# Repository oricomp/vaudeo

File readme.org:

#+title: vaudeo

A Video and Audio Board for the OriComp System

#+CAPTION: Vaudeo Logo
#+ATTR_ORG: :align center
#+ATTR_HTML: :align center
[[https://github.com/oricomp/vaudeo/blob/main/docs/logo/vaudeo_logo_gray.png]]

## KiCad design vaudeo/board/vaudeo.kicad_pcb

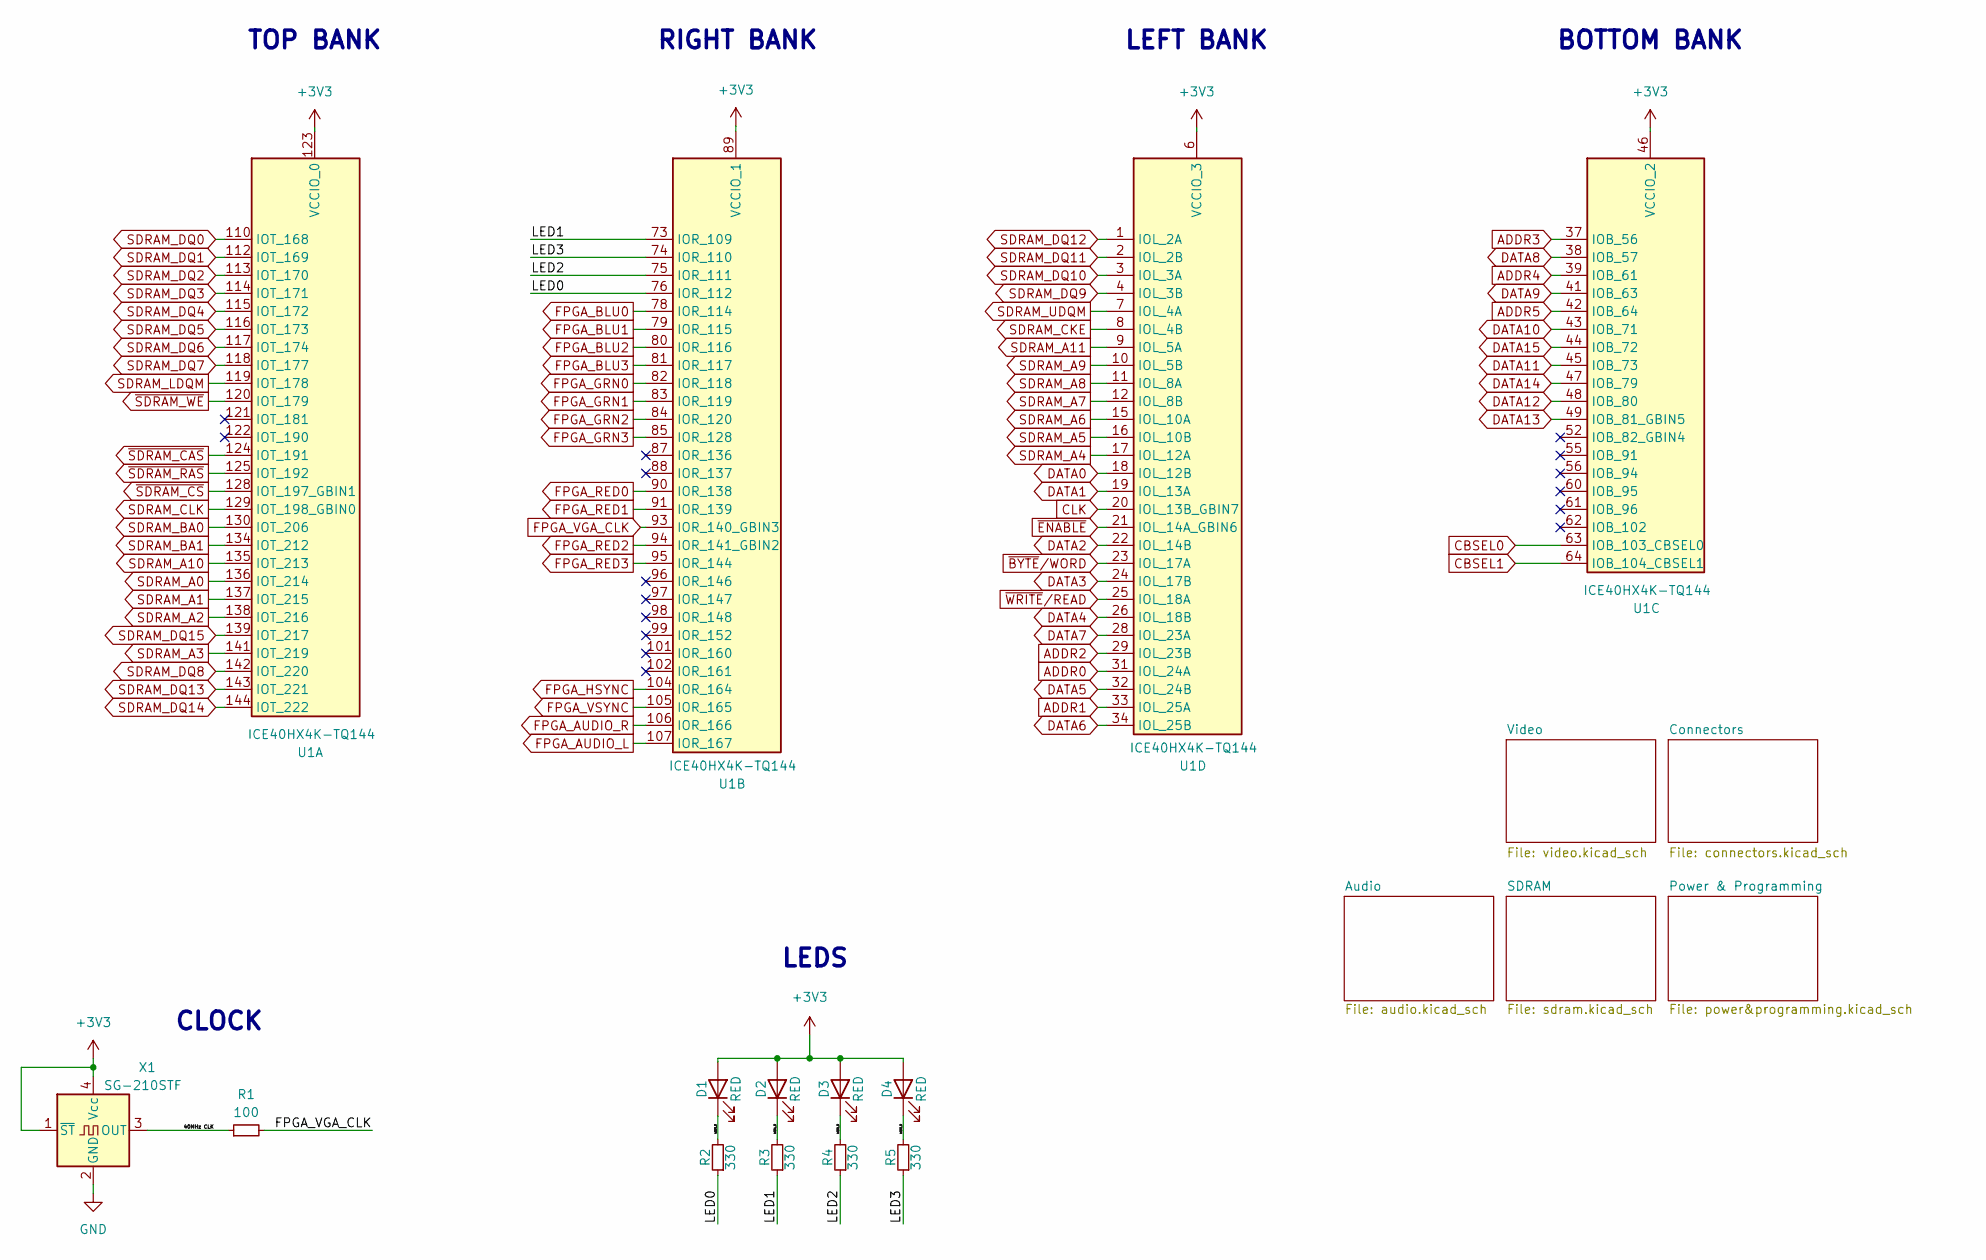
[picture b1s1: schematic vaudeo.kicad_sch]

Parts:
D1, D2, D3, D4: RED; D_0805_2012Metric
R1: 100; R_0805_2012Metric_Pad1.20x1.40mm_HandSolder
R2, R3, R4, R5: 330; R_0805_2012Metric_Pad1.20x1.40mm_HandSolder
U1: ICE40HX4K-TQ144; TQFP-144_20x20mm_P0.5mm
X1: SG-210STF; Oscillator_SMD_SeikoEpson_SG210-4Pin_2.5x2.0mm

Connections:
+3V3: D1.2 (A), D2.2 (A), D3.2 (A), D4.2 (A), U1.6 (VCCIO_3), U1.30 (VCCIO_3), U1.46 (VCCIO_2), U1.57 (VCCIO_2), U1.89 (VCCIO_1), U1.100 (VCCIO_1), U1.123 (VCCIO_0), U1.131 (VCCIO_0), X1.1 (~ST), X1.4 (Vcc); also elsewhere on the board
/40MHz CLK: R1.1, X1.3 (OUT)
/LED0: R2.1, U1.76 (IOR_112)
/LED0_R: D1.1 (K), R2.2
/LED1: R3.1, U1.73 (IOR_109)
/LED1_R: D2.1 (K), R3.2
/LED2: R4.1, U1.75 (IOR_111)
/LED2_R: D3.1 (K), R4.2
/LED3: R5.1, U1.74 (IOR_110)
/LED3_R: D4.1 (K), R5.2
ADDR0: U1.31 (IOL_24A); also elsewhere on the board
ADDR1: U1.33 (IOL_25A); also elsewhere on the board
ADDR2: U1.29 (IOL_23B); also elsewhere on the board
ADDR3: U1.37 (IOB_56); also elsewhere on the board
ADDR4: U1.39 (IOB_61); also elsewhere on the board
ADDR5: U1.42 (IOB_64); also elsewhere on the board
CBSEL0: U1.63 (IOB_103_CBSEL0); also elsewhere on the board
CBSEL1: U1.64 (IOB_104_CBSEL1); also elsewhere on the board
CLK: U1.20 (IOL_13B_GBIN7); also elsewhere on the board
DATA0: U1.18 (IOL_12B); also elsewhere on the board
DATA1: U1.19 (IOL_13A); also elsewhere on the board
DATA2: U1.22 (IOL_14B); also elsewhere on the board
DATA3: U1.24 (IOL_17B); also elsewhere on the board
DATA4: U1.26 (IOL_18B); also elsewhere on the board
DATA5: U1.32 (IOL_24B); also elsewhere on the board
DATA6: U1.34 (IOL_25B); also elsewhere on the board
DATA7: U1.28 (IOL_23A); also elsewhere on the board
DATA8: U1.38 (IOB_57); also elsewhere on the board
DATA9: U1.41 (IOB_63); also elsewhere on the board
DATA10: U1.43 (IOB_71); also elsewhere on the board
DATA11: U1.45 (IOB_73); also elsewhere on the board
DATA12: U1.48 (IOB_80); also elsewhere on the board
DATA13: U1.49 (IOB_81_GBIN5); also elsewhere on the board
DATA14: U1.47 (IOB_79); also elsewhere on the board
DATA15: U1.44 (IOB_72); also elsewhere on the board
FPGA_AUDIO_L: U1.107 (IOR_167); also elsewhere on the board
FPGA_AUDIO_R: U1.106 (IOR_166); also elsewhere on the board
FPGA_BLU0: U1.78 (IOR_114); also elsewhere on the board
FPGA_BLU1: U1.79 (IOR_115); also elsewhere on the board
FPGA_BLU2: U1.80 (IOR_116); also elsewhere on the board
FPGA_BLU3: U1.81 (IOR_117); also elsewhere on the board
FPGA_GRN0: U1.82 (IOR_118); also elsewhere on the board
FPGA_GRN1: U1.83 (IOR_119); also elsewhere on the board
FPGA_GRN2: U1.84 (IOR_120); also elsewhere on the board
FPGA_GRN3: U1.85 (IOR_128); also elsewhere on the board
FPGA_HSYNC: U1.104 (IOR_164); also elsewhere on the board
FPGA_RED0: U1.90 (IOR_138); also elsewhere on the board
FPGA_RED1: U1.91 (IOR_139); also elsewhere on the board
FPGA_RED2: U1.94 (IOR_141_GBIN2); also elsewhere on the board
FPGA_RED3: U1.95 (IOR_144); also elsewhere on the board
FPGA_VGA_CLK: R1.2, U1.93 (IOR_140_GBIN3)
FPGA_VSYNC: U1.105 (IOR_165); also elsewhere on the board
GND: X1.2 (GND); also elsewhere on the board
SDRAM_A0: U1.136 (IOT_214); also elsewhere on the board
SDRAM_A1: U1.137 (IOT_215); also elsewhere on the board
SDRAM_A2: U1.138 (IOT_216); also elsewhere on the board
SDRAM_A3: U1.141 (IOT_219); also elsewhere on the board
SDRAM_A4: U1.17 (IOL_12A); also elsewhere on the board
SDRAM_A5: U1.16 (IOL_10B); also elsewhere on the board
SDRAM_A6: U1.15 (IOL_10A); also elsewhere on the board
SDRAM_A7: U1.12 (IOL_8B); also elsewhere on the board
SDRAM_A8: U1.11 (IOL_8A); also elsewhere on the board
SDRAM_A9: U1.10 (IOL_5B); also elsewhere on the board
SDRAM_A10: U1.135 (IOT_213); also elsewhere on the board
SDRAM_A11: U1.9 (IOL_5A); also elsewhere on the board
SDRAM_BA0: U1.130 (IOT_206); also elsewhere on the board
SDRAM_BA1: U1.134 (IOT_212); also elsewhere on the board
SDRAM_CKE: U1.8 (IOL_4B); also elsewhere on the board
SDRAM_CLK: U1.129 (IOT_198_GBIN0); also elsewhere on the board
SDRAM_DQ0: U1.110 (IOT_168); also elsewhere on the board
SDRAM_DQ1: U1.112 (IOT_169); also elsewhere on the board
SDRAM_DQ2: U1.113 (IOT_170); also elsewhere on the board
SDRAM_DQ3: U1.114 (IOT_171); also elsewhere on the board
SDRAM_DQ4: U1.115 (IOT_172); also elsewhere on the board
SDRAM_DQ5: U1.116 (IOT_173); also elsewhere on the board
SDRAM_DQ6: U1.117 (IOT_174); also elsewhere on the board
SDRAM_DQ7: U1.118 (IOT_177); also elsewhere on the board
SDRAM_DQ8: U1.142 (IOT_220); also elsewhere on the board
SDRAM_DQ9: U1.4 (IOL_3B); also elsewhere on the board
SDRAM_DQ10: U1.3 (IOL_3A); also elsewhere on the board
SDRAM_DQ11: U1.2 (IOL_2B); also elsewhere on the board
SDRAM_DQ12: U1.1 (IOL_2A); also elsewhere on the board
SDRAM_DQ13: U1.143 (IOT_221); also elsewhere on the board
SDRAM_DQ14: U1.144 (IOT_222); also elsewhere on the board
SDRAM_DQ15: U1.139 (IOT_217); also elsewhere on the board
SDRAM_LDQM: U1.119 (IOT_178); also elsewhere on the board
SDRAM_UDQM: U1.7 (IOL_4A); also elsewhere on the board
~BYTE/WORD: U1.23 (IOL_17A); also elsewhere on the board
~ENABLE: U1.21 (IOL_14A_GBIN6); also elsewhere on the board
~SDRAM_CAS: U1.124 (IOT_191); also elsewhere on the board
~SDRAM_CS: U1.128 (IOT_197_GBIN1); also elsewhere on the board
~SDRAM_RAS: U1.125 (IOT_192); also elsewhere on the board
~SDRAM_WE: U1.120 (IOT_179); also elsewhere on the board

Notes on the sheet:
CLOCK
TOP BANK
LEFT BANK
RIGHT BANK
LEDS
BOTTOM BANK

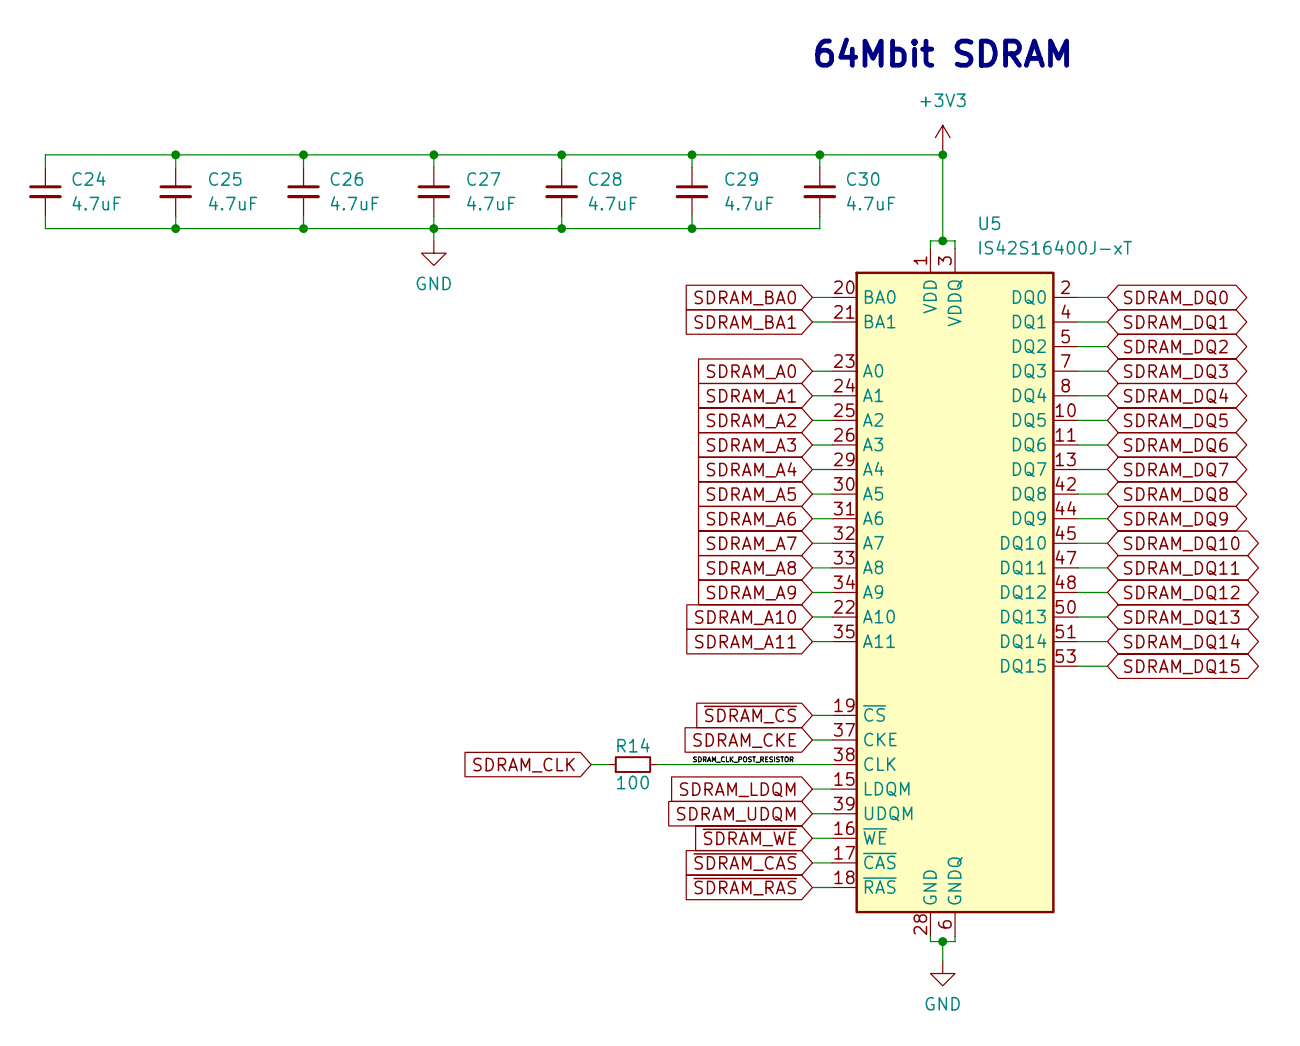
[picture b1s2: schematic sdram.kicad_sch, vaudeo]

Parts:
C24, C25, C26, C27, C28, C29, C30: 4.7uF; C_0805_2012Metric_Pad1.18x1.45mm_HandSolder
R14: 100; R_0805_2012Metric_Pad1.20x1.40mm_HandSolder
U5: IS42S16400J-xT; TSOP-II-54_22.2x10.16mm_P0.8mm

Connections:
+3V3: C24.1, C25.1, C26.1, C27.1, C28.1, C29.1, C30.1, U5.1 (VDD), U5.3 (VDDQ), U5.9 (VDDQ), U5.14 (VDD), U5.27 (VDD), U5.43 (VDDQ), U5.49 (VDDQ); also elsewhere on the board
/SDRAM/SDRAM_CLK_POST_RESISTOR: R14.2, U5.38 (CLK)
GND: C24.2, C25.2, C26.2, C27.2, C28.2, C29.2, C30.2, U5.6 (GNDQ), U5.12 (GNDQ), U5.28 (GND), U5.41 (GND), U5.46 (GNDQ), U5.52 (GNDQ), U5.54 (GND); also elsewhere on the board
SDRAM_A0: U5.23 (A0); also elsewhere on the board
SDRAM_A1: U5.24 (A1); also elsewhere on the board
SDRAM_A2: U5.25 (A2); also elsewhere on the board
SDRAM_A3: U5.26 (A3); also elsewhere on the board
SDRAM_A4: U5.29 (A4); also elsewhere on the board
SDRAM_A5: U5.30 (A5); also elsewhere on the board
SDRAM_A6: U5.31 (A6); also elsewhere on the board
SDRAM_A7: U5.32 (A7); also elsewhere on the board
SDRAM_A8: U5.33 (A8); also elsewhere on the board
SDRAM_A9: U5.34 (A9); also elsewhere on the board
SDRAM_A10: U5.22 (A10); also elsewhere on the board
SDRAM_A11: U5.35 (A11); also elsewhere on the board
SDRAM_BA0: U5.20 (BA0); also elsewhere on the board
SDRAM_BA1: U5.21 (BA1); also elsewhere on the board
SDRAM_CKE: U5.37 (CKE); also elsewhere on the board
SDRAM_CLK: R14.1; also elsewhere on the board
SDRAM_DQ0: U5.2 (DQ0); also elsewhere on the board
SDRAM_DQ1: U5.4 (DQ1); also elsewhere on the board
SDRAM_DQ2: U5.5 (DQ2); also elsewhere on the board
SDRAM_DQ3: U5.7 (DQ3); also elsewhere on the board
SDRAM_DQ4: U5.8 (DQ4); also elsewhere on the board
SDRAM_DQ5: U5.10 (DQ5); also elsewhere on the board
SDRAM_DQ6: U5.11 (DQ6); also elsewhere on the board
SDRAM_DQ7: U5.13 (DQ7); also elsewhere on the board
SDRAM_DQ8: U5.42 (DQ8); also elsewhere on the board
SDRAM_DQ9: U5.44 (DQ9); also elsewhere on the board
SDRAM_DQ10: U5.45 (DQ10); also elsewhere on the board
SDRAM_DQ11: U5.47 (DQ11); also elsewhere on the board
SDRAM_DQ12: U5.48 (DQ12); also elsewhere on the board
SDRAM_DQ13: U5.50 (DQ13); also elsewhere on the board
SDRAM_DQ14: U5.51 (DQ14); also elsewhere on the board
SDRAM_DQ15: U5.53 (DQ15); also elsewhere on the board
SDRAM_LDQM: U5.15 (LDQM); also elsewhere on the board
SDRAM_UDQM: U5.39 (UDQM); also elsewhere on the board
~SDRAM_CAS: U5.17 (~CAS); also elsewhere on the board
~SDRAM_CS: U5.19 (~CS); also elsewhere on the board
~SDRAM_RAS: U5.18 (~RAS); also elsewhere on the board
~SDRAM_WE: U5.16 (~WE); also elsewhere on the board

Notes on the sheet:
64Mbit SDRAM

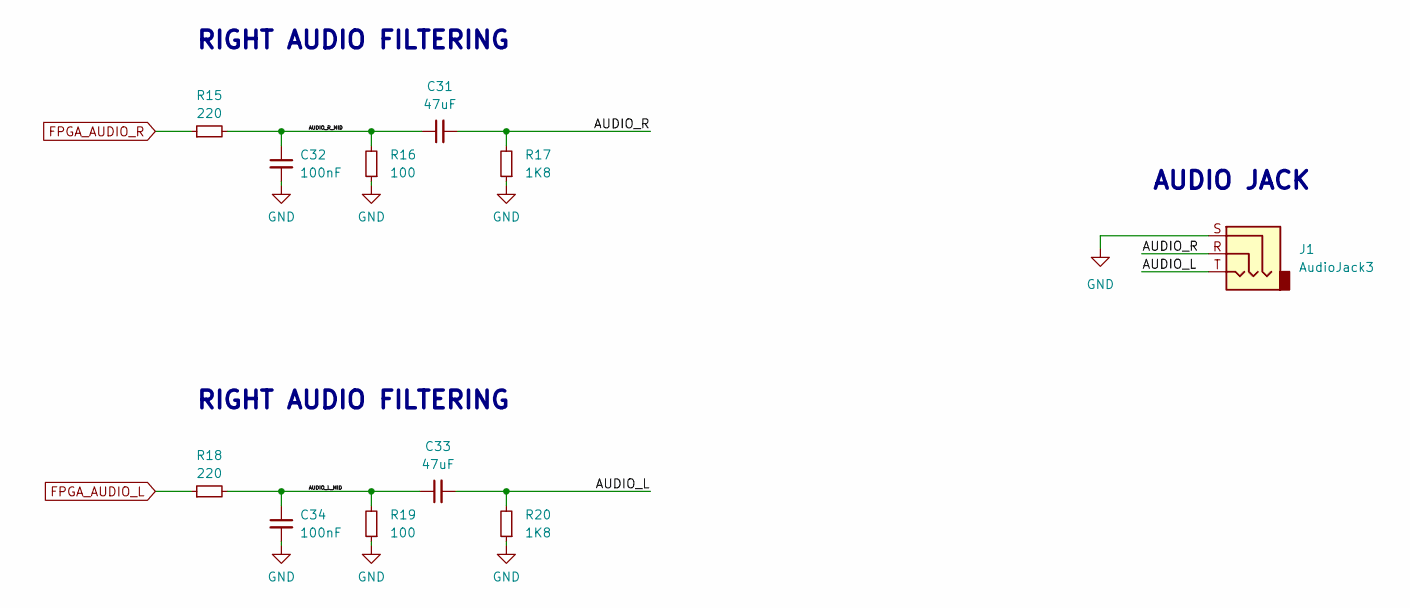
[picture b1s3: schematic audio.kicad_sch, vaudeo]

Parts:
C31, C33: 47uF; C_0805_2012Metric_Pad1.18x1.45mm_HandSolder
C32, C34: 100nF; C_0805_2012Metric_Pad1.18x1.45mm_HandSolder
J1: AudioJack3; Jack_3.5mm_CUI_SJ-3523-SMT_Horizontal
R15, R18: 220; R_0805_2012Metric_Pad1.20x1.40mm_HandSolder
R16, R19: 100; R_0805_2012Metric_Pad1.20x1.40mm_HandSolder
R17, R20: 1K8; R_0805_2012Metric_Pad1.20x1.40mm_HandSolder

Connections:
/Audio/AUDIO_L: C33.2, J1.T, R20.2
/Audio/AUDIO_L_MID: C33.1, C34.1, R18.2, R19.2
/Audio/AUDIO_R: C31.2, J1.R, R17.2
/Audio/AUDIO_R_MID: C31.1, C32.1, R15.2, R16.2
FPGA_AUDIO_L: R18.1; also elsewhere on the board
FPGA_AUDIO_R: R15.1; also elsewhere on the board
GND: C32.2, C34.2, J1.S, R16.1, R17.1, R19.1, R20.1; also elsewhere on the board

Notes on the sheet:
AUDIO JACK
RIGHT AUDIO FILTERING

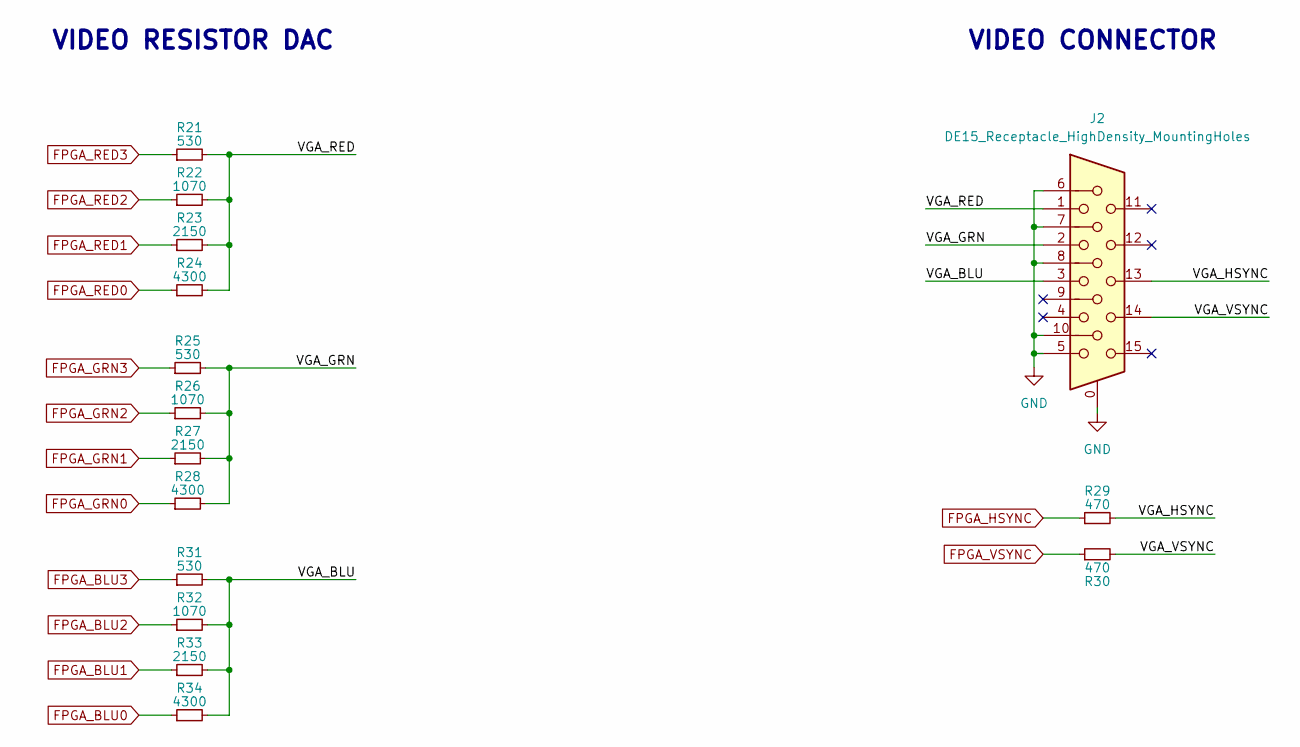
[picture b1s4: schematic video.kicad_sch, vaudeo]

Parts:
J2: DE15_Receptacle_HighDensity_MountingHoles; DSUB-15-HD_Female_Horizontal_P2.29x1.98mm_EdgePinOffset8.35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
R21, R25, R31: 530; R_0805_2012Metric_Pad1.20x1.40mm_HandSolder
R22, R26, R32: 1070; R_0805_2012Metric_Pad1.20x1.40mm_HandSolder
R23, R27, R33: 2150; R_0805_2012Metric_Pad1.20x1.40mm_HandSolder
R24, R28, R34: 4300; R_0805_2012Metric_Pad1.20x1.40mm_HandSolder
R29, R30: 470; R_0805_2012Metric_Pad1.20x1.40mm_HandSolder

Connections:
/Video/VGA_BLU: J2.3, R31.2, R32.2, R33.2, R34.2
/Video/VGA_GRN: J2.2, R25.2, R26.2, R27.2, R28.2
/Video/VGA_HSYNC: J2.13, R29.2
/Video/VGA_RED: J2.1, R21.2, R22.2, R23.2, R24.2
/Video/VGA_VSYNC: J2.14, R30.2
FPGA_BLU0: R34.1; also elsewhere on the board
FPGA_BLU1: R33.1; also elsewhere on the board
FPGA_BLU2: R32.1; also elsewhere on the board
FPGA_BLU3: R31.1; also elsewhere on the board
FPGA_GRN0: R28.1; also elsewhere on the board
FPGA_GRN1: R27.1; also elsewhere on the board
FPGA_GRN2: R26.1; also elsewhere on the board
FPGA_GRN3: R25.1; also elsewhere on the board
FPGA_HSYNC: R29.1; also elsewhere on the board
FPGA_RED0: R24.1; also elsewhere on the board
FPGA_RED1: R23.1; also elsewhere on the board
FPGA_RED2: R22.1; also elsewhere on the board
FPGA_RED3: R21.1; also elsewhere on the board
FPGA_VSYNC: R30.1; also elsewhere on the board
GND: J2.0, J2.5, J2.6, J2.7, J2.8, J2.10; also elsewhere on the board

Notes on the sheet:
VIDEO RESISTOR DAC
VIDEO CONNECTOR

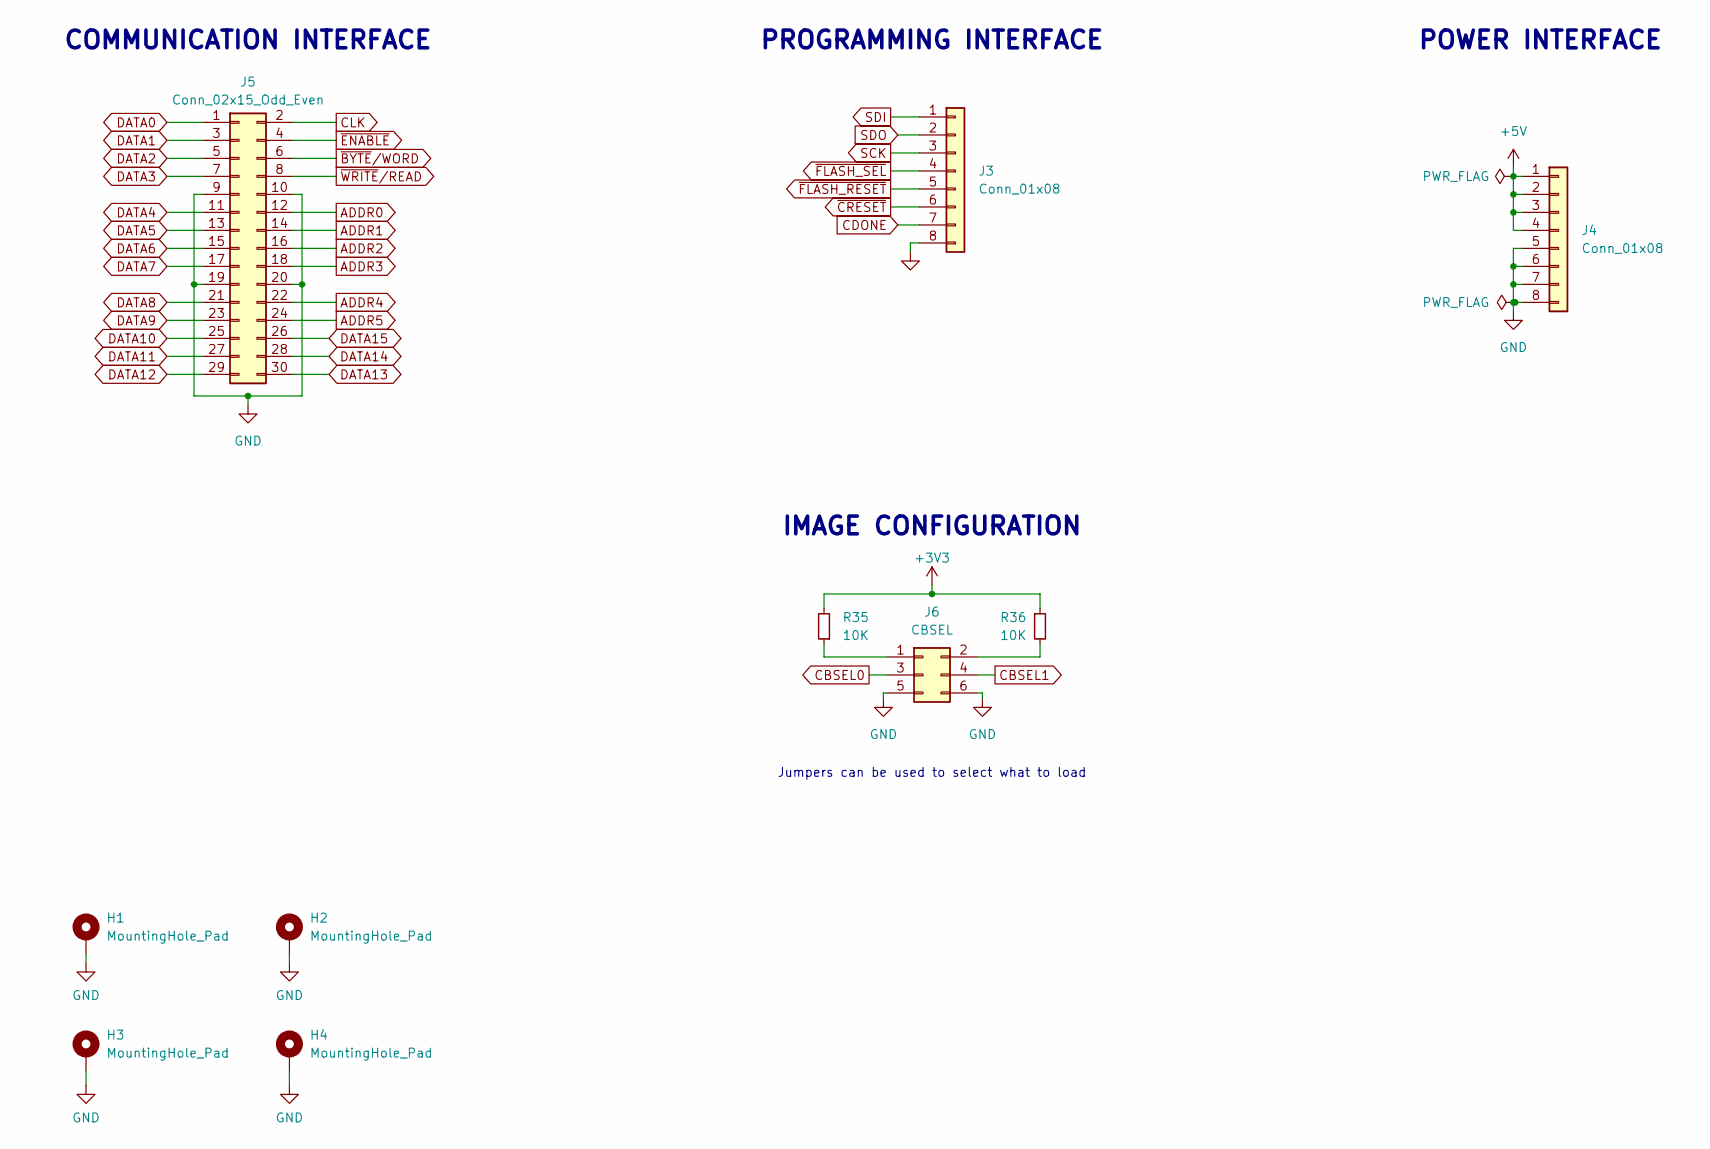
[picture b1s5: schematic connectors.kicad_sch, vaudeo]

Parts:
H1, H2, H3, H4: MountingHole_Pad; MountingHole_3.2mm_M3_Pad_Via
J3, J4: Conn_01x08; PinHeader_1x08_P2.54mm_Vertical
J5: Conn_02x15_Odd_Even; PinHeader_2x15_P2.54mm_Vertical
J6: CBSEL; PinHeader_2x03_P2.54mm_Vertical
R35, R36: 10K; R_0805_2012Metric_Pad1.20x1.40mm_HandSolder

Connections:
+3V3: R35.2, R36.1; also elsewhere on the board
+5V: J4.1, J4.2, J4.3, J4.4; also elsewhere on the board
ADDR0: J5.12; also elsewhere on the board
ADDR1: J5.14; also elsewhere on the board
ADDR2: J5.16; also elsewhere on the board
ADDR3: J5.18; also elsewhere on the board
ADDR4: J5.22; also elsewhere on the board
ADDR5: J5.24; also elsewhere on the board
CBSEL0: J6.3; also elsewhere on the board
CBSEL1: J6.4; also elsewhere on the board
CDONE: J3.7; also elsewhere on the board
CLK: J5.2; also elsewhere on the board
DATA0: J5.1; also elsewhere on the board
DATA1: J5.3; also elsewhere on the board
DATA2: J5.5; also elsewhere on the board
DATA3: J5.7; also elsewhere on the board
DATA4: J5.11; also elsewhere on the board
DATA5: J5.13; also elsewhere on the board
DATA6: J5.15; also elsewhere on the board
DATA7: J5.17; also elsewhere on the board
DATA8: J5.21; also elsewhere on the board
DATA9: J5.23; also elsewhere on the board
DATA10: J5.25; also elsewhere on the board
DATA11: J5.27; also elsewhere on the board
DATA12: J5.29; also elsewhere on the board
DATA13: J5.30; also elsewhere on the board
DATA14: J5.28; also elsewhere on the board
DATA15: J5.26; also elsewhere on the board
GND: H1.1, H2.1, H3.1, H4.1, J3.8, J4.5, J4.6, J4.7, J4.8, J5.9, J5.10, J5.19, J5.20, J6.5, J6.6; also elsewhere on the board
unnamed: J6.1, R35.1
unnamed: J6.2, R36.2
SCK: J3.3; also elsewhere on the board
SDI: J3.1; also elsewhere on the board
SDO: J3.2; also elsewhere on the board
~BYTE/WORD: J5.6; also elsewhere on the board
~CRESET: J3.6; also elsewhere on the board
~ENABLE: J5.4; also elsewhere on the board
~FLASH_RESET: J3.5; also elsewhere on the board
~FLASH_SEL: J3.4; also elsewhere on the board

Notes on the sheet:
POWER INTERFACE
IMAGE CONFIGURATION
COMMUNICATION INTERFACE
PROGRAMMING INTERFACE
Jumpers can be used to select what to load

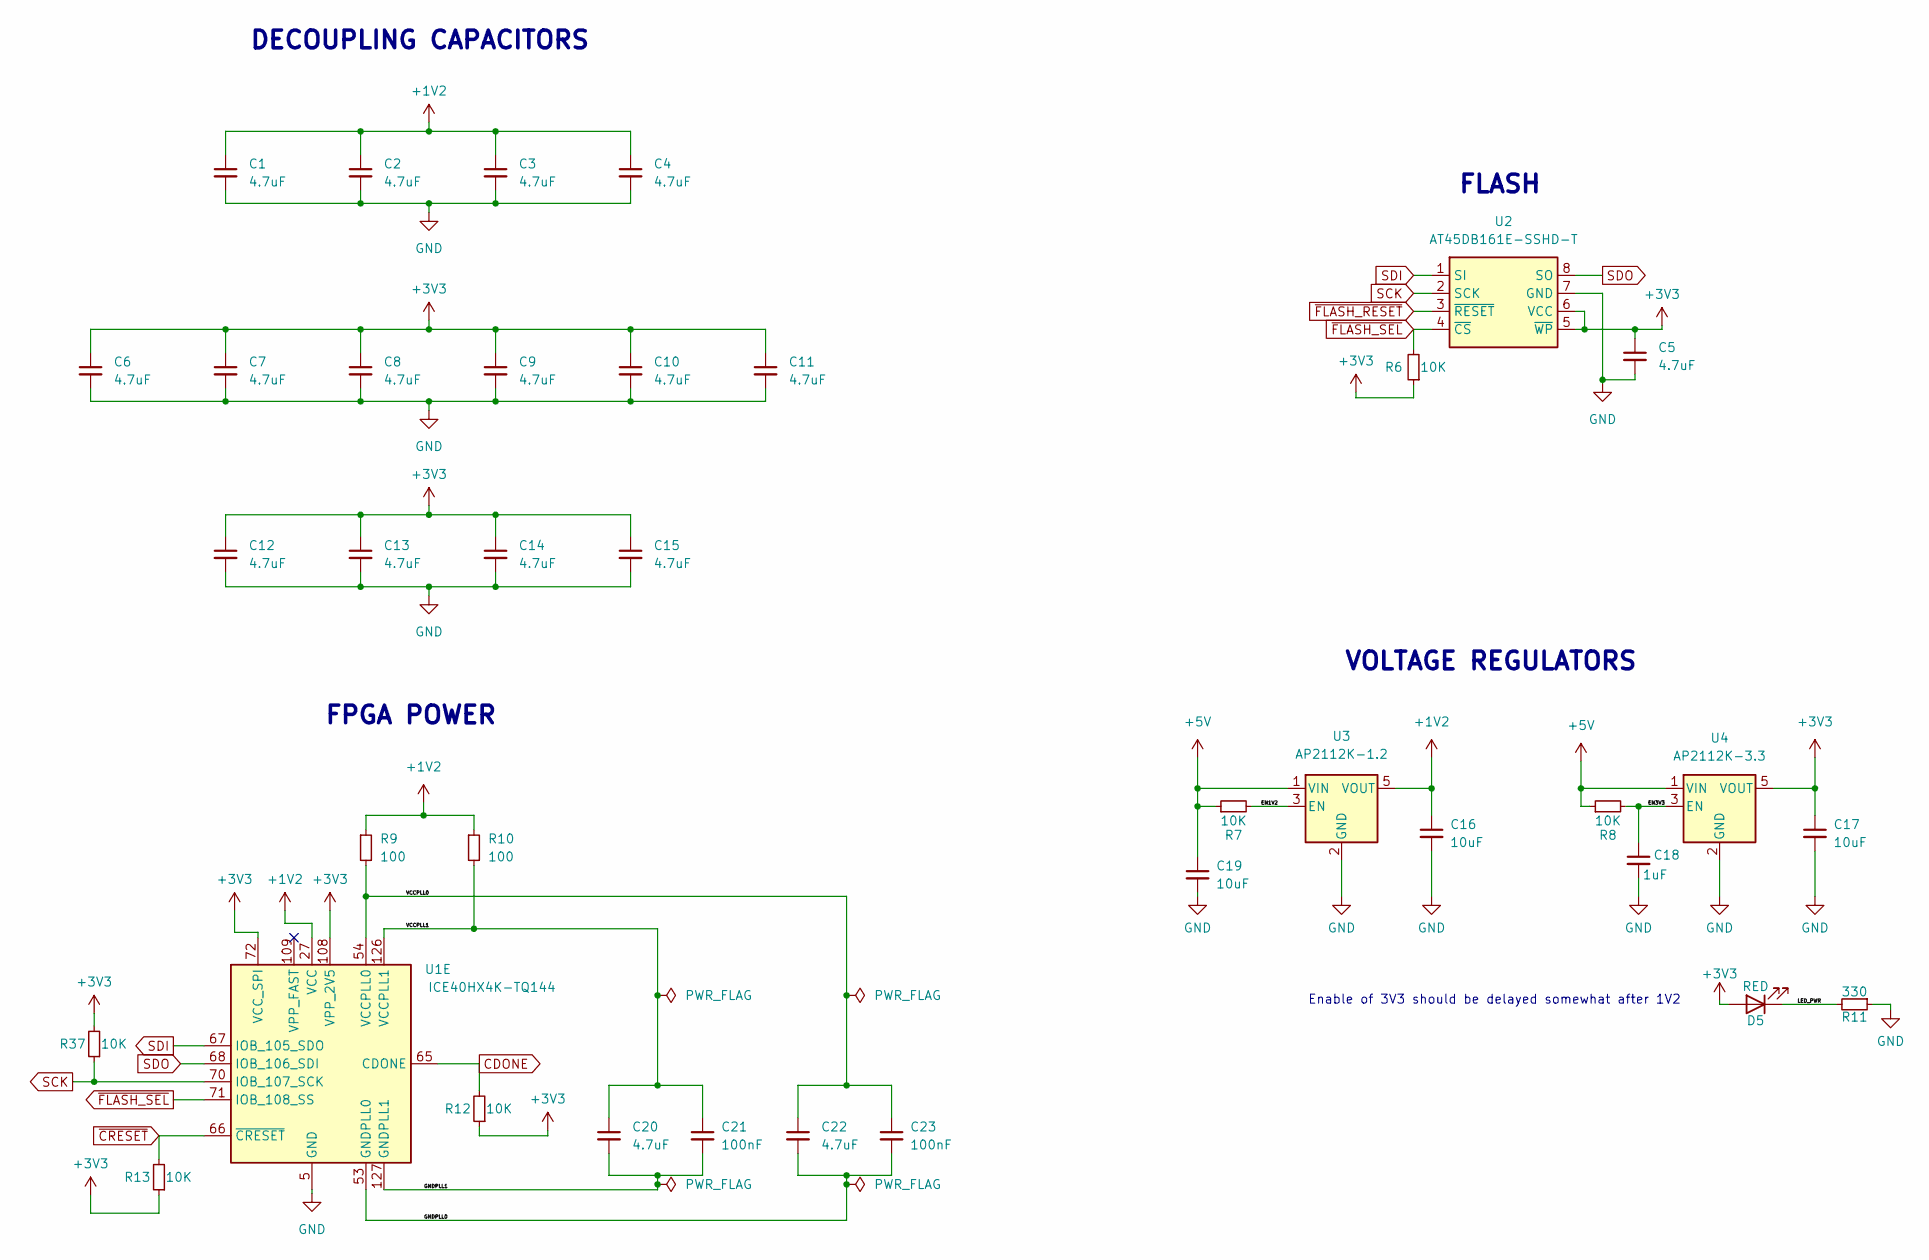
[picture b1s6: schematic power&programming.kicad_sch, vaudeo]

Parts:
C1, C2, C3, C4, C5, C6, C7, C8, C9, C10, C11, C12, C13, C14, C15, C20, C22: 4.7uF; C_0805_2012Metric_Pad1.18x1.45mm_HandSolder
C16, C17, C19: 10uF; C_0805_2012Metric_Pad1.18x1.45mm_HandSolder
C18: 1uF; C_0805_2012Metric_Pad1.18x1.45mm_HandSolder
C21, C23: 100nF; C_0805_2012Metric_Pad1.18x1.45mm_HandSolder
D5: RED; D_0805_2012Metric
R6, R7, R8, R12, R13, R37: 10K; R_0805_2012Metric_Pad1.20x1.40mm_HandSolder
R9, R10: 100; R_0805_2012Metric_Pad1.20x1.40mm_HandSolder
R11: 330; R_0805_2012Metric_Pad1.20x1.40mm_HandSolder
U1: ICE40HX4K-TQ144; TQFP-144_20x20mm_P0.5mm
U2: AT45DB161E-SSHD-T; SOIC-8_3.9x4.9mm_P1.27mm
U3: AP2112K-1.2; SOT-23-5
U4: AP2112K-3.3; SOT-23-5

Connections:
+1V2: C1.1, C2.1, C3.1, C4.1, C16.1, R9.1, R10.1, U1.27 (VCC), U1.40 (VCC), U1.92 (VCC), U1.111 (VCC), U3.5 (VOUT)
+3V3: C5.1, C6.1, C7.1, C8.1, C9.1, C10.1, C11.1, C12.1, C13.1, C14.1, C15.1, C17.1, D5.2 (A), R6.1, R12.1, R13.1, R37.2, U1.72 (VCC_SPI), U1.108 (VPP_2V5), U2.5 (~WP), U2.6 (VCC), U4.5 (VOUT); also elsewhere on the board
+5V: C19.1, R7.1, R8.1, U3.1 (VIN), U4.1 (VIN); also elsewhere on the board
/Power & Programming/EN1V2: R7.2, U3.3 (EN)
/Power & Programming/EN3V3: C18.1, R8.2, U4.3 (EN)
/Power & Programming/GNDPLL0: C22.2, C23.2, U1.53 (GNDPLL0)
/Power & Programming/GNDPLL1: C20.2, C21.2, U1.127 (GNDPLL1)
/Power & Programming/LED_PWR: D5.1 (K), R11.2
/Power & Programming/VCCPLL0: C22.1, C23.1, R9.2, U1.54 (VCCPLL0)
/Power & Programming/VCCPLL1: C20.1, C21.1, R10.2, U1.126 (VCCPLL1)
CDONE: R12.2, U1.65 (CDONE); also elsewhere on the board
GND: C1.2, C2.2, C3.2, C4.2, C5.2, C6.2, C7.2, C8.2, C9.2, C10.2, C11.2, C12.2, C13.2, C14.2, C15.2, C16.2, C17.2, C18.2, C19.2, R11.1, U1.5 (GND), U1.13 (GND), U1.14 (GND), U1.59 (GND), U1.69 (GND), U1.86 (GND), U1.103 (GND), U1.132 (GND), U1.140 (GND), U2.7 (GND), U3.2 (GND), U4.2 (GND); also elsewhere on the board
SCK: R37.1, U1.70 (IOB_107_SCK), U2.2 (SCK); also elsewhere on the board
SDI: U1.67 (IOB_105_SDO), U2.1 (SI); also elsewhere on the board
SDO: U1.68 (IOB_106_SDI), U2.8 (SO); also elsewhere on the board
~CRESET: R13.2, U1.66 (~CRESET); also elsewhere on the board
~FLASH_RESET: U2.3 (~RESET); also elsewhere on the board
~FLASH_SEL: R6.2, U1.71 (IOB_108_SS), U2.4 (~CS); also elsewhere on the board

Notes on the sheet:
FPGA POWER
FLASH
VOLTAGE REGULATORS
Enable of 3V3 should be delayed somewhat after 1V2
DECOUPLING CAPACITORS

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
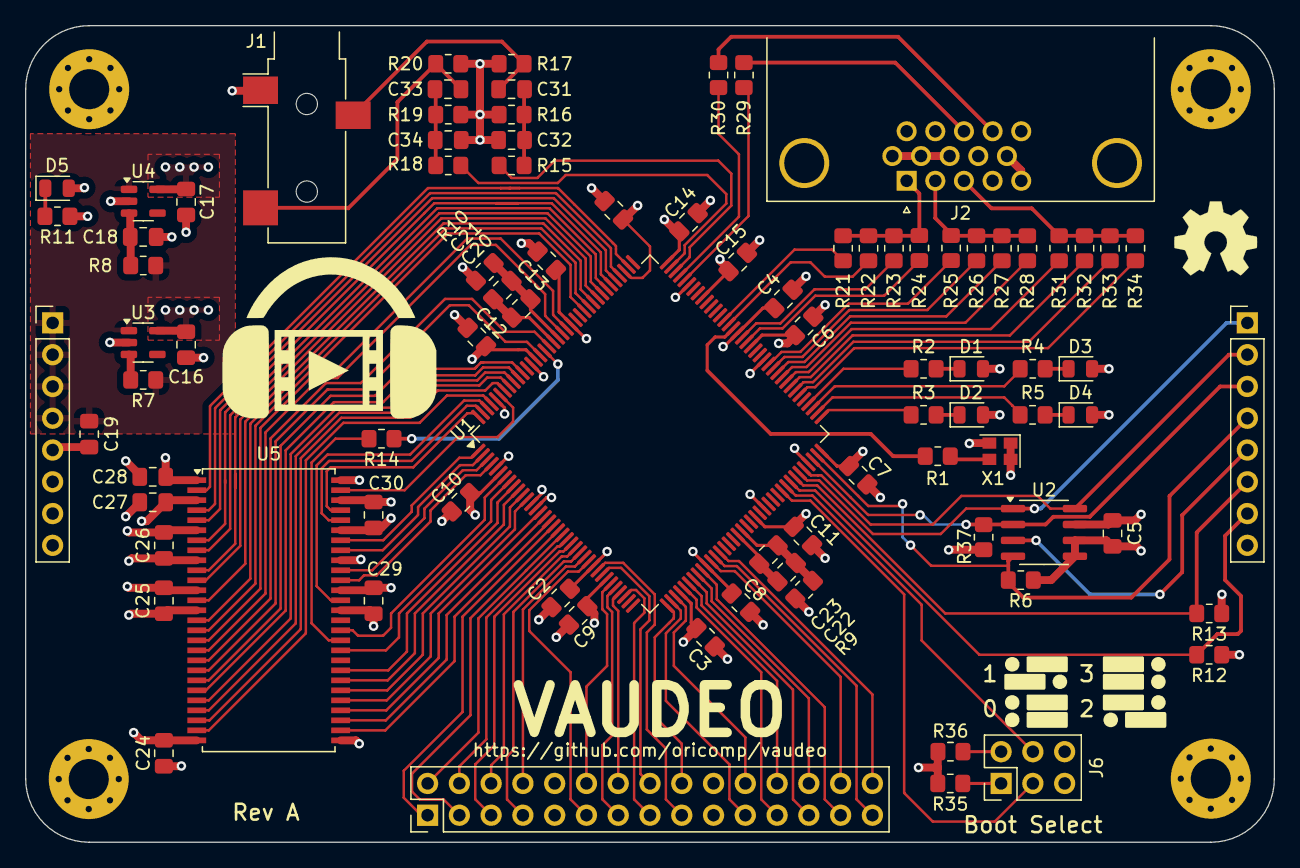
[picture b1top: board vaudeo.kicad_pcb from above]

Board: 4 copper layers, 99.8 x 65.3 mm, 92 parts (0 on the bottom side), 122 nets.
